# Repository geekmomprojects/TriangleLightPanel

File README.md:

# TriangleLightPanel

Files for modular "Nanoleaf" style connecting LED PCBs. Each triangular board contains three 4020 Side-Emitting SK6812 LEDs, which diffuse their light into a translucent acrylic cover panel. The triangular LED boards are connected via smaller rectangular connector PCBs using a system of pressure contacts and pads. 

This repository contains Eagle CAD files for the Triangle LED boards and connector boards. Be warned that SMT soldering 4020 side-emitting LEDs is *very* tricky if you decide to make your own. Best accomplished with solder paste and a reflow oven or hot air gun

A thin layer of 1/16" clear acrylic across the back of each Triangle PCB prevents pressure contacts from being crushed and a layer of 1/8" semi-translucent acrylic diffuses the LEDs on the front side. CAD files for each are included and will need to be laser cut. Link to best diffusion acrylic I've found to use is in the BOM.

All pieces held together with M2 screws (10mm) and nuts. The full assembly can stand freely without being wall mounted.

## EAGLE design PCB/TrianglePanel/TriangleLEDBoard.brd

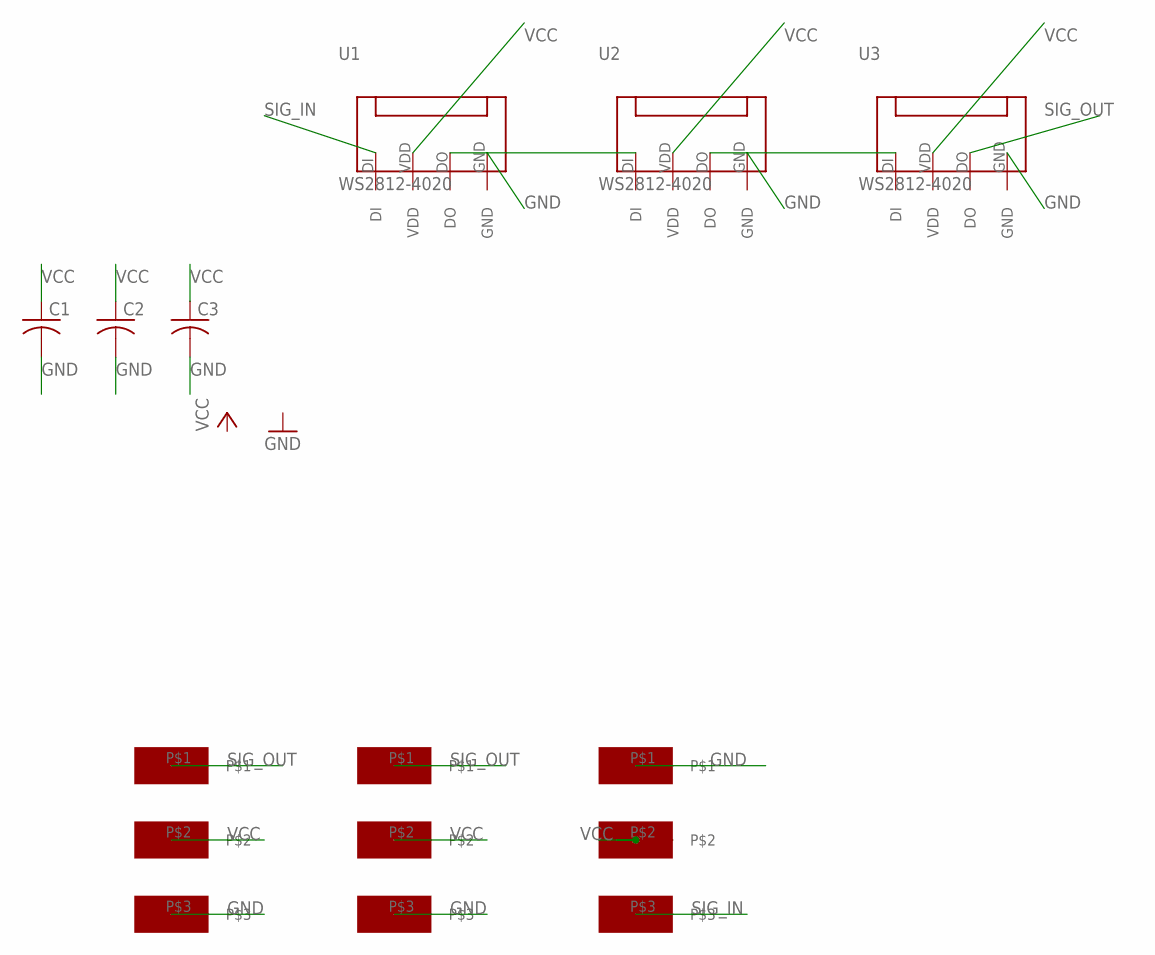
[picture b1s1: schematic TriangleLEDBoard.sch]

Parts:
C1, C2, C3: C-USC0603; C0603
U1, U2, U3: WS2812-4020; WS2812B_4020
U$1, U$2, U$3: 3_CONTACT_PADS_5_MM_SPACING_WITH_HOLES; RECTANGULAR_PADS_5_MM_SPACING_WITH_HOLES

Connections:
GND: C1.2, C2.2, C3.2, U1.GND, U2.GND, U3.GND, U$1.P$1, U$2.P$3, U$3.P$3
unnamed: U1.DO, U2.DI
unnamed: U2.DO, U3.DI
SIG_IN: U1.DI, U$1.P$3
SIG_OUT: U3.DO, U$2.P$1, U$3.P$1
VCC: C1.1, C2.1, C3.1, U1.VDD, U2.VDD, U3.VDD, U$1.P$2, U$2.P$2, U$3.P$2

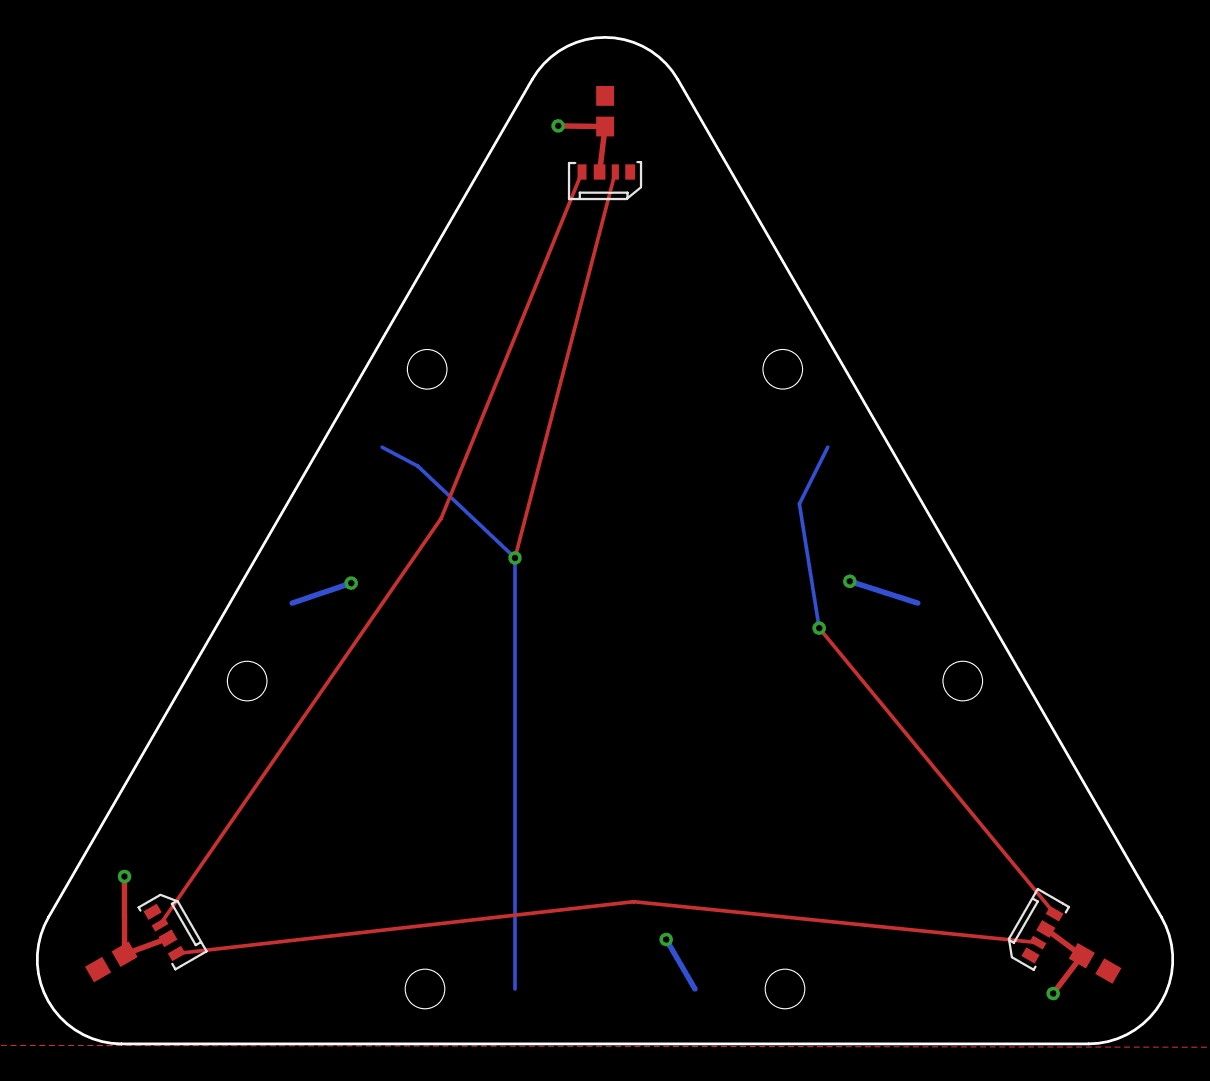
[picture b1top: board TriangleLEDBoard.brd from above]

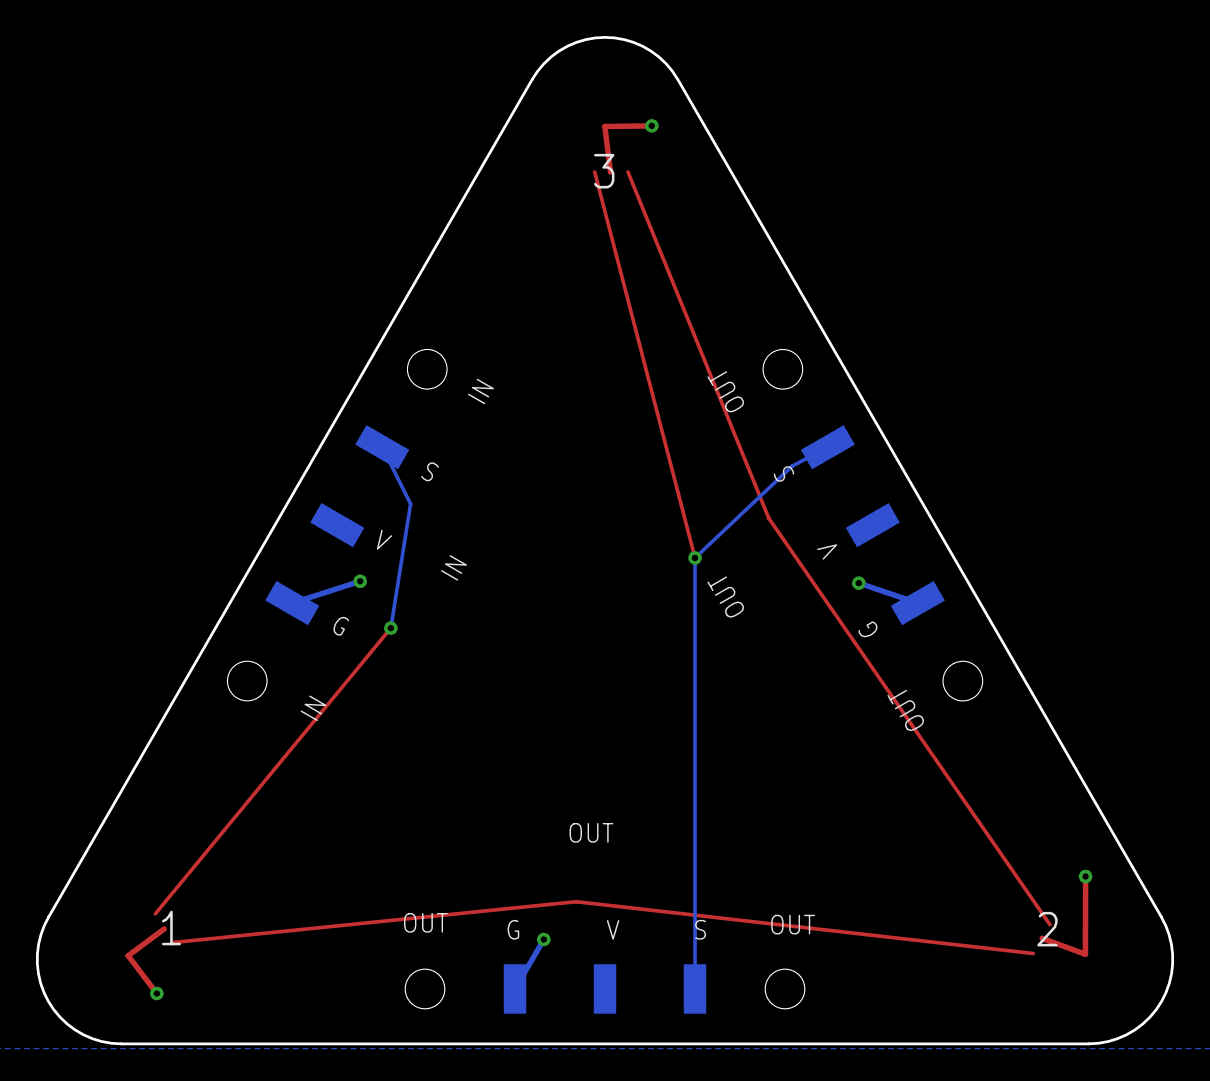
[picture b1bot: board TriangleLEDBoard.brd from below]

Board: 2 copper layers, 63.1 x 55.9 mm, 9 parts (3 on the bottom side), 6 nets.

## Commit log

2020-06-08 Add design files
    Adding design files to repository
2020-06-08 Add images
2020-07-28 Update FileDescriptions.txt
    spelling
